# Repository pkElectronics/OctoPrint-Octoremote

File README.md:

# OctoPrint-Octoremote

## Work in Progress! Use with care ##

Octoremote is a system to control serveral functions of your printer with a simple press of a button. Control the axis movement, manual extrusion and homing without the need of navigating through the printer menu or opening the Octopi GUI in your browser. 

OctoRemote consists of two components, the Octoprint plugin and an arduino based hardware controller. The controller and the plugin communicate through a serial connection using a simple byte-based protocol. As OctoRemote is based on Octoprint it is totally printer independent and works easily with any Octorprint compatible printer. At the moment following printer actions are implemented:

* Homing X&Y and Z
* Moving of all axis
* Extrude/Retract material
* Stop Print
* Pause Print
* Start/Resume Print
* Select Extruder
* Select movement distance (4 options)
* User programmable keys Supporting custom GCODE and OctoPrint Scripting

## Setup

Install via the bundled [Plugin Manager](https://github.com/foosel/OctoPrint/wiki/Plugin:-Plugin-Manager)
or manually using this URL:

    https://github.com/pkElectronics/OctoPrint-Octoremote/archive/master.zip

The plugin repository also contains the source code of the Arduino program which is necessary for the hardware controller. Installation if described in detail in the Hardware section.

## Configuration

Use the OctoRemote Plugin page from the Octoprint settings to adjust the parameters to your needs. 

The correct setting for the Comport field is something you have to figure out for yourself, using either for example the Windows device manager or the /dev/tty/\* files under linux. Usually an Arduino UNO will appear as something like /dev/ttyACM0. 

The default settings were developed and tested using an Anet A8 printer.

## Usage

It´s pretty easy, wait for Octoprint to start and start hitting the buttons, movement distance starts at Stage 1 and goes up until Stage 4 with each keypress. From Stage 4 it jumps back to 1. Same holds true for the extruder selection except that it wraps around when the number of configured extruders is reached. Keep in mind that extruding and retracting material only works if the hotend has the right temperature.

## Hardware

There are two possible hardware configurations available, a simple breadboard version using an Arduino UNO, a 4x4 matrix keypad and 8 leds. 

Of course you could build the circuit in a different way, you just have to change the pin assignments in the software.

If you stick to the recommended schematic you will end up with a key assignment like this:

Please Note: User Key 1 is only available when the Tool/Extruder count is 1. Otherwise the key is used to switch between extruders.

In the future there will also be a custom made PCB which includes all necessary parts and uses cherry mx switches for the keys. If you are interested in getting a custom OctoRemote Board
feel free to contact me.
The device is still be compatible with the Arduino IDE for easy upgrading and hacking. Development of the Controller is in pre-production state and will be heading for Kickstarter soon.

Regardless of the type of the used hardware, programming is done using the Arduino IDE and the sourcecodes from the arduino/OctoRemote/ folder.

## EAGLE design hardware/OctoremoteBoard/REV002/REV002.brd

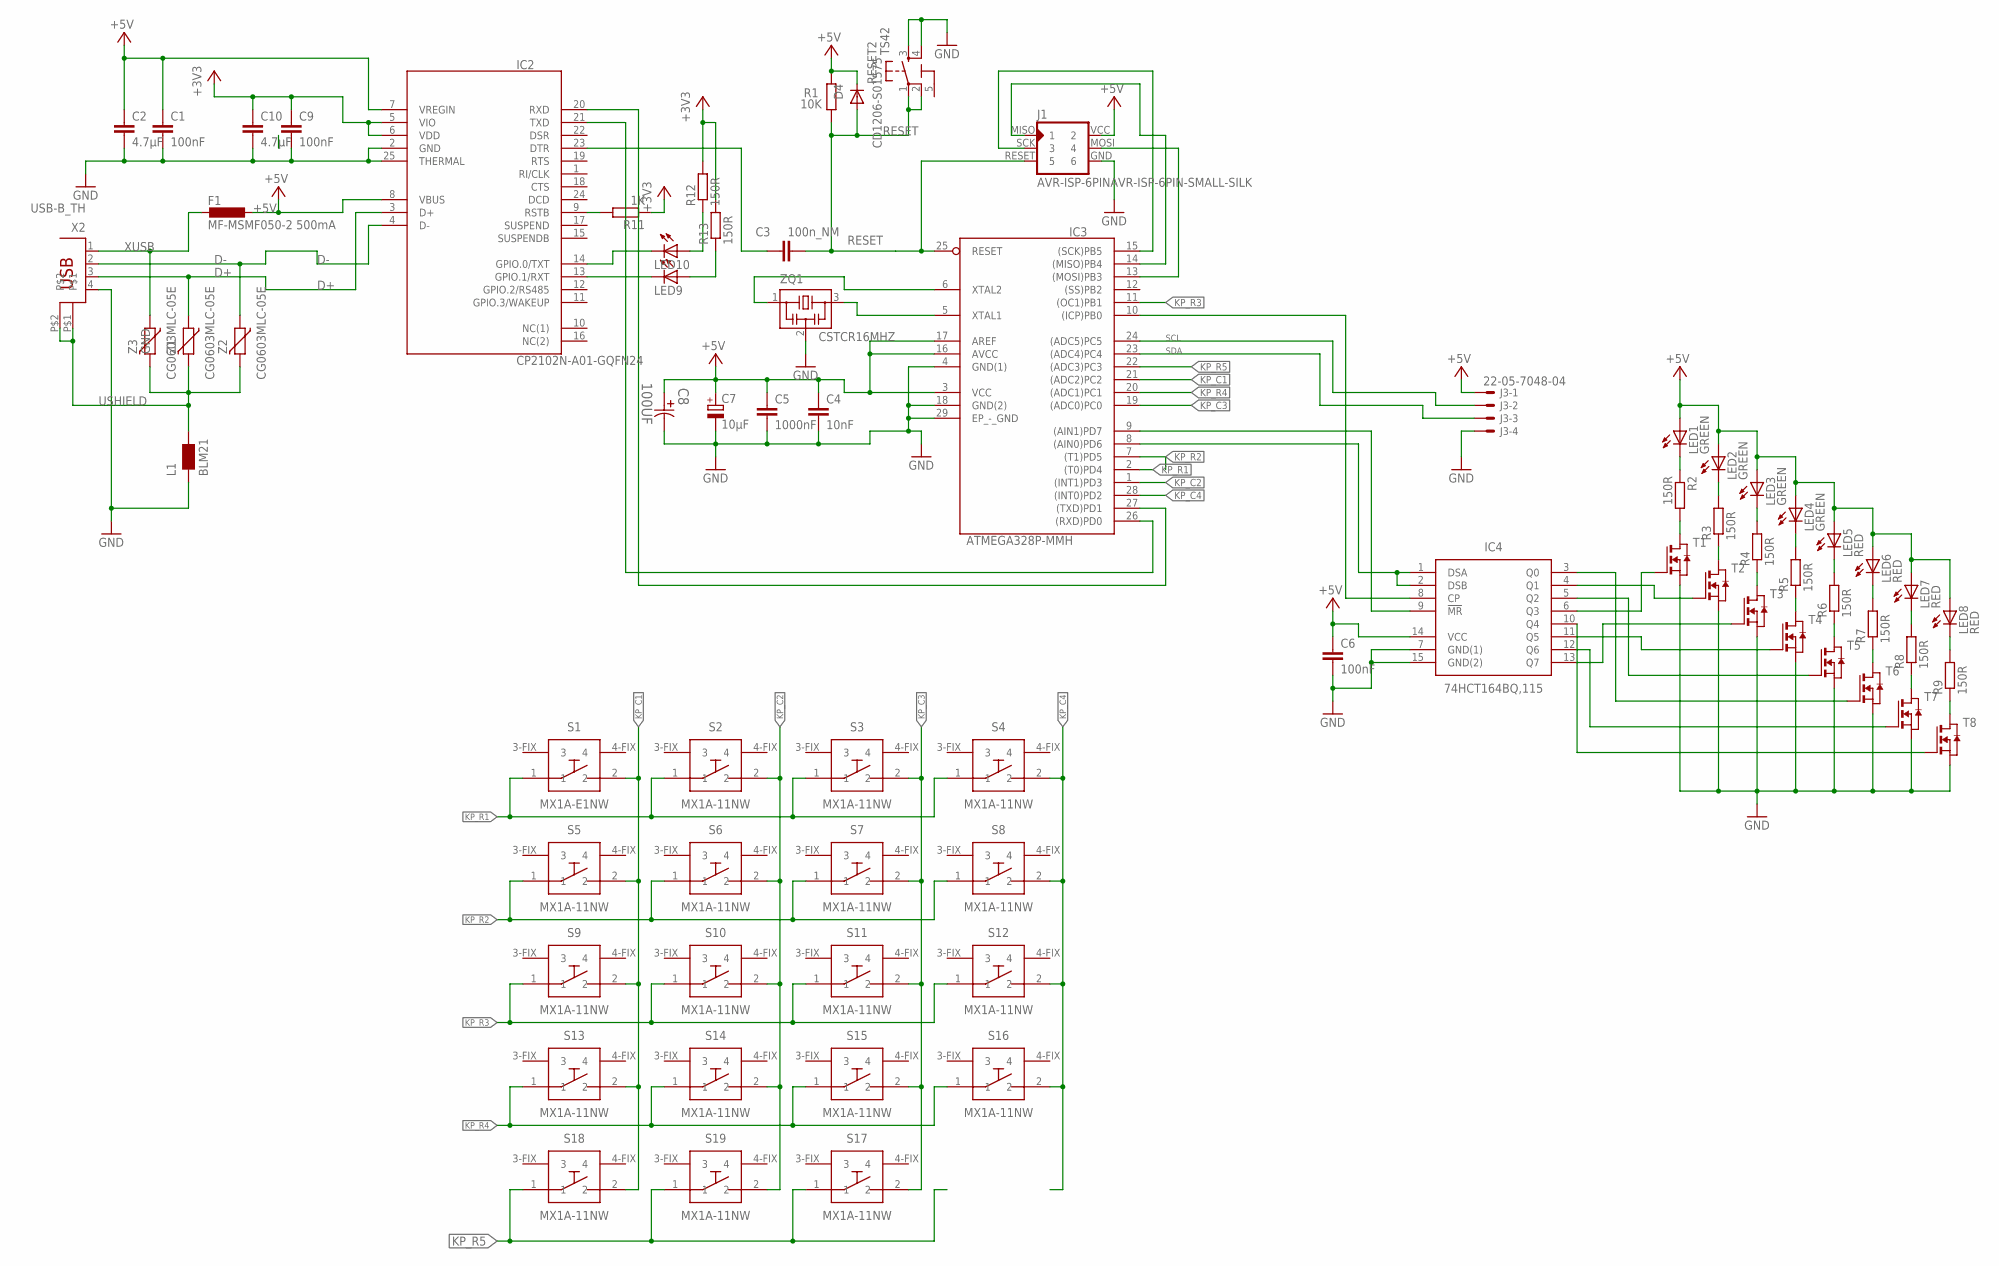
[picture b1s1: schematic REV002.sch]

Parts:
C1, C6, C9: 100nF; C0603K
C2, C10: 4.7µF; C0603K
C3: 100n_NM; C0603K
C4: 10nF; C0603K
C5: 1000nF; C0603K
C7: 10µF; SMC_B
C8: 100UF; CAPAE430X610N
D4: CD1206-S01575; MINIMELF
F1: MF-MSMF050-2 500mA; L1812
IC2: CP2102N-A01-GQFN24; QFN50P400X400X80-25N
IC3: ATMEGA328P-MMH; QFN45P400X400X100-29N
IC4: 74HCT164BQ,115; QFN50P300X250X100-15N
J1: AVR-ISP-6PINAVR-ISP-6PIN-SMALL-SILK; AVR-ISP-6PIN-SMAILL-SILK
J3: 22-05-7048-04; 7395-04
L1: BLM21; 0805
LED1, LED2, LED3, LED4: GREEN; P-LCC-2
LED5, LED6, LED7, LED8: RED; P-LCC-2
LED9, LED10: LEDCHIPLED_0603; CHIPLED_0603
R1: 10K; R0603
R2, R3, R4, R5, R6, R7, R8, R9, R12, R13: 150R; R0603
R11: 1K; R0603
RESET2: TS42
S1: MX1A-E1NW; MX1A-11NW_1
S2, S3, S4, S5, S6, S7, S8, S9, S10, S11, S12, S13, S14, S15, S16, S17, S18, S19: MX1A-11NW; MX1A-11NW_1
T1, T2, T3, T4, T5, T6, T7, T8: NMOSSOT23; SOT-23
X2: USB-B_TH; PN61729
Z1, Z2, Z3: CG0603MLC-05E; CT/CN0603
ZQ1: CSTCR16MHZ; CSTER12M

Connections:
5-GND: RESET2.5 (5-GND)
+3V3: C9.1, C10.1, IC2.5 (VIO), IC2.6 (VDD), R11.1, R12.2, R13.2
+5V: C1.1, C2.1, C4.1, C5.1, C6.1, C7.+, C8.1, D4.C, F1.1, IC2.7 (VREGIN), IC2.8 (VBUS), IC3.3 (VCC), IC3.16 (AVCC), IC3.17 (AREF), IC4.14 (VCC), J1.VCC (2), J3.1, LED1.A, LED2.A, LED3.A, LED4.A, LED5.A, LED6.A, LED7.A, LED8.A, R1.2
D+: IC2.3 (D+), X2.3, Z1.1
D-: IC2.4 (D-), X2.2, Z2.1
GND: C1.2, C2.2, C4.2, C5.2, C6.2, C7.-, C8.2, C9.2, C10.2, IC2.2 (GND), IC2.25 (THERMAL), IC3.4 (GND(1)), IC3.18 (GND(2)), IC3.29 (EP_-_GND), IC4.7 (GND(1)), IC4.15 (GND(2)), J1.GND (6), J3.4, L1.1, RESET2.3, RESET2.4, T1.2 (S), T2.2 (S), T3.2 (S), T4.2 (S), T5.2 (S), T6.2 (S), T7.2 (S), T8.2 (S), X2.4, ZQ1.2
KP_C1: IC3.21 ((ADC2)PC2), S1.2, S5.2, S9.2, S13.2, S18.2
KP_C2: IC3.1 ((INT1)PD3), S2.2, S6.2, S10.2, S14.2, S19.2
KP_C3: IC3.19 ((ADC0)PC0), S3.2, S7.2, S11.2, S15.2, S17.2
KP_C4: IC3.28 ((INT0)PD2), S4.2, S8.2, S12.2, S16.2
KP_R1: IC3.2 ((T0)PD4), S1.1, S2.1, S3.1, S4.1
KP_R2: IC3.7 ((T1)PD5), S5.1, S6.1, S7.1, S8.1
KP_R3: IC3.11 ((OC1)PB1), S9.1, S10.1, S11.1, S12.1
KP_R4: IC3.20 ((ADC1)PC1), S13.1, S14.1, S15.1, S16.1
KP_R5: IC3.22 ((ADC3)PC3), S17.1, S18.1, S19.1
LED1-: LED1.C, R2.1
LED2+: IC3.13 ((MOSI)PB3), J1.MOSI (4)
LED3+: IC3.14 ((MISO)PB4), J1.MISO (1)
LED4+: IC3.15 ((SCK)PB5), J1.SCK (3)
unnamed: IC4.6 (Q3), T1.3 (G)
unnamed: IC2.9 (RSTB), R11.2
unnamed: C3.2, IC2.23 (DTR)
unnamed: IC2.14 (GPIO.0/TXT), LED10.C
unnamed: IC2.13 (GPIO.1/RXT), LED9.C
unnamed: LED10.A, R12.1
unnamed: LED9.A, R13.1
unnamed: IC4.4 (Q1), T2.3 (G)
unnamed: R2.2, T1.1 (D)
unnamed: IC4.13 (Q7), T3.3 (G)
unnamed: IC4.11 (Q5), T4.3 (G)
unnamed: IC4.5 (Q2), T5.3 (G)
unnamed: IC4.3 (Q0), T6.3 (G)
unnamed: IC4.12 (Q6), T7.3 (G)
unnamed: IC4.10 (Q4), T8.3 (G)
unnamed: LED2.C, R3.2
unnamed: R3.1, T2.1 (D)
unnamed: R4.1, T3.1 (D)
unnamed: R5.1, T4.1 (D)
unnamed: R6.1, T5.1 (D)
unnamed: R7.1, T6.1 (D)
unnamed: R8.1, T7.1 (D)
unnamed: R9.1, T8.1 (D)
unnamed: LED8.C, R9.2
unnamed: LED7.C, R8.2
unnamed: LED6.C, R7.2
unnamed: LED5.C, R6.2
unnamed: LED4.C, R5.2
unnamed: LED3.C, R4.2
unnamed: IC3.10 ((ICP)PB0), IC4.8 (CP)
unnamed: IC3.8 ((AIN0)PD6), IC4.1 (DSA), IC4.2 (DSB)
unnamed: IC3.9 ((AIN1)PD7), IC4.9 (!MR)
RESET: C3.1, D4.A, IC3.25 (RESET), J1.RESET (5), R1.1, RESET2.1, RESET2.2
RX: IC2.20 (RXD), IC3.27 ((TXD)PD1)
SCL: IC3.24 ((ADC5)PC5), J3.2
SDA: IC3.23 ((ADC4)PC4), J3.3
TX: IC2.21 (TXD), IC3.26 ((RXD)PD0)
USHIELD: L1.2, X2.P$1, X2.P$2, Z1.2, Z2.2, Z3.2
XTAL1: IC3.5 (XTAL1), ZQ1.3
XTAL2: IC3.6 (XTAL2), ZQ1.1
XUSB: F1.2, X2.1, Z3.1

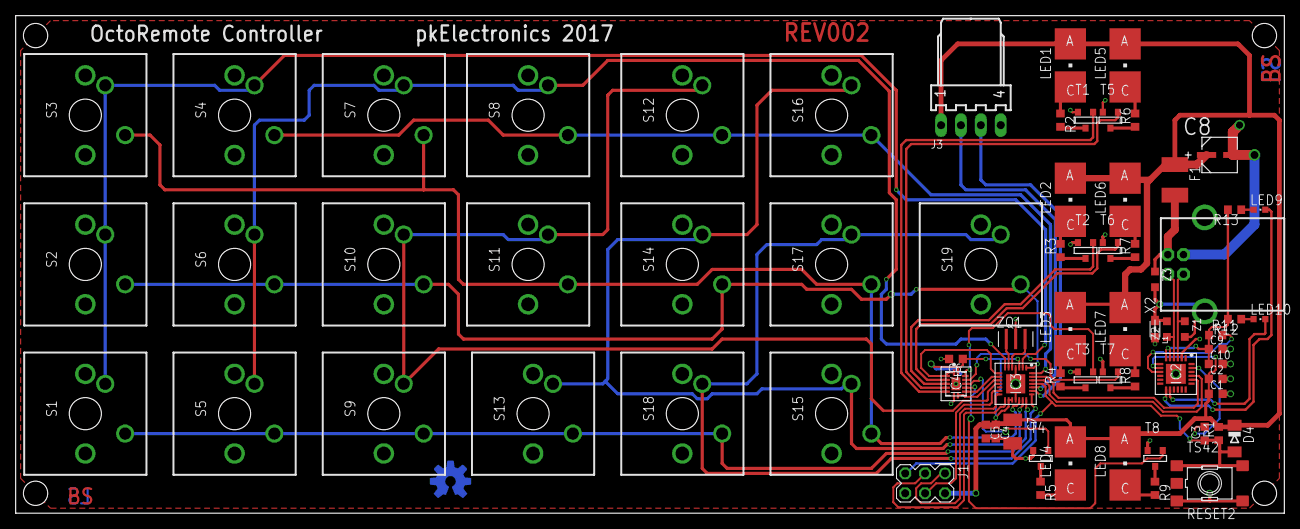
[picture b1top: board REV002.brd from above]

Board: 2 copper layers, 161.9 x 63.5 mm, 74 parts (1 on the bottom side), 59 nets.

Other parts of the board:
U$1: OSHWLOGO_TOP_0.2

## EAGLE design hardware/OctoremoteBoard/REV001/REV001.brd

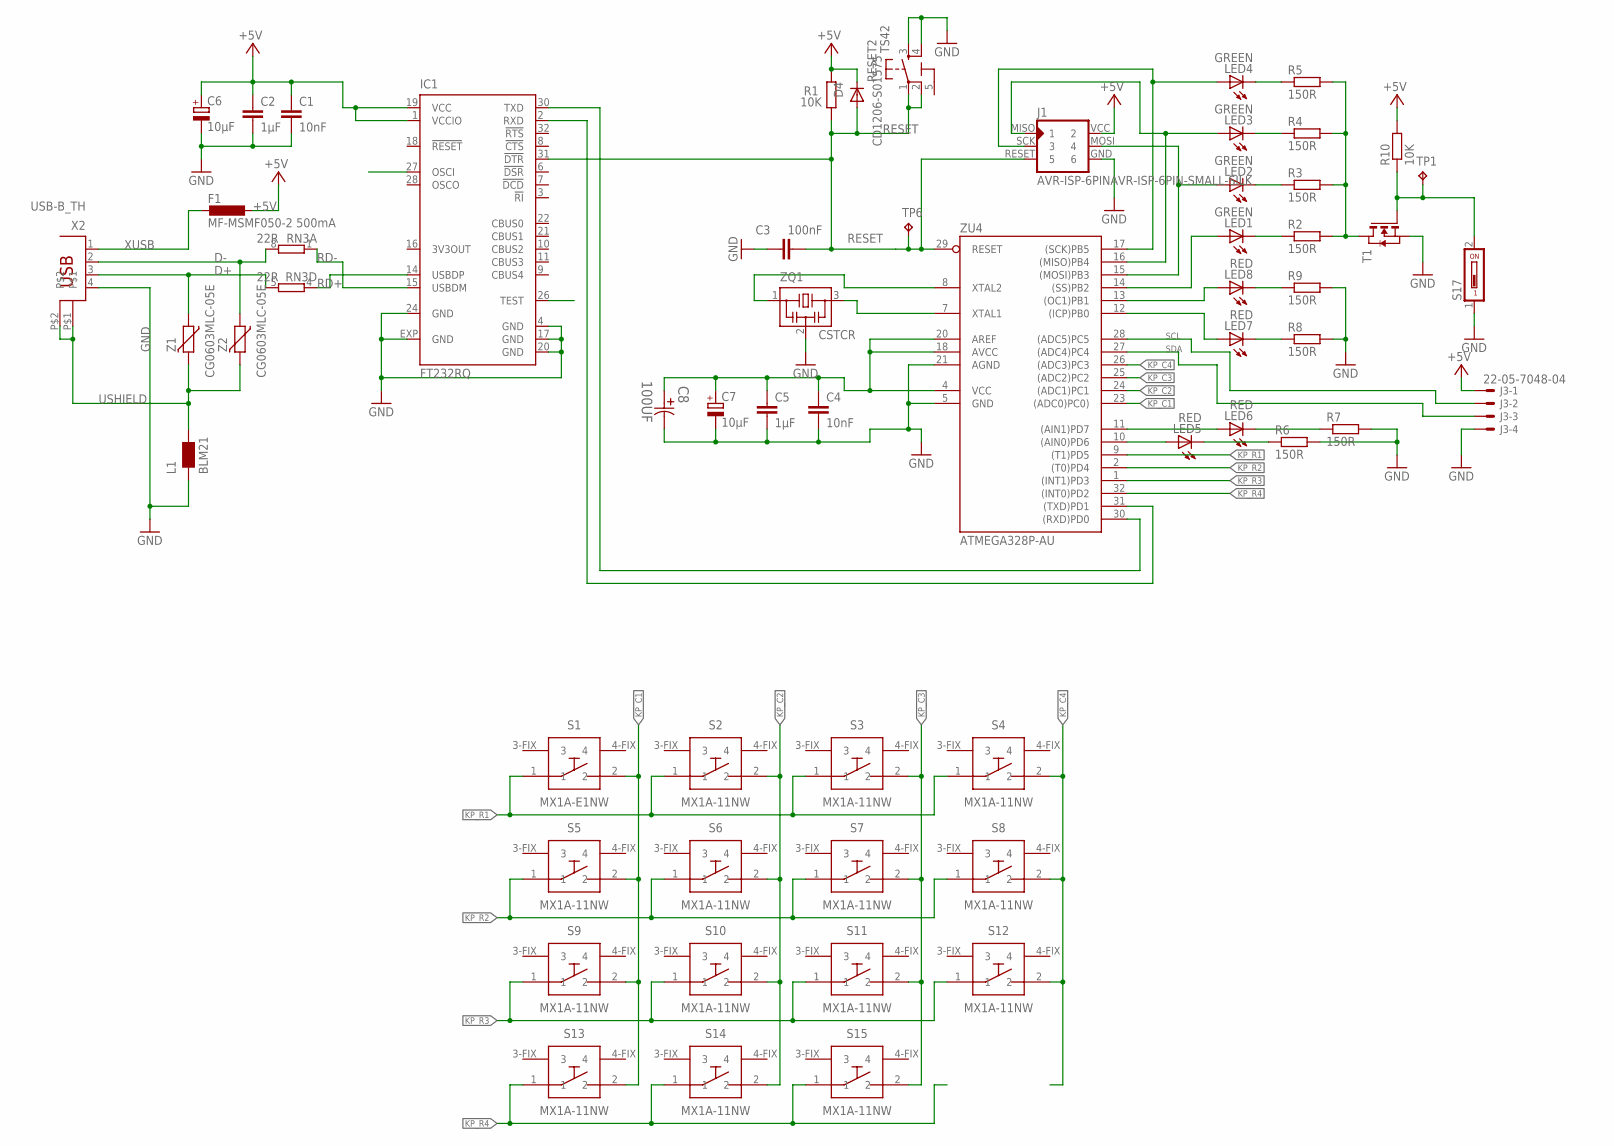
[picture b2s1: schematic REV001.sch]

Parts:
C1, C4: 10nF; C0603K
C2, C5: 1µF; C0603K
C3: 100nF; C0603-ROUND
C6, C7: 10µF; SMC_B
C8: 100UF; CAPAE430X610N
D4: CD1206-S01575; MINIMELF
F1: MF-MSMF050-2 500mA; L1812
IC1: FT232RQ; QFN32
J1: AVR-ISP-6PINAVR-ISP-6PIN-SMALL-SILK; AVR-ISP-6PIN-SMAILL-SILK
J3: 22-05-7048-04; 7395-04
L1: BLM21; 0805
LED1, LED2, LED3, LED4: GREEN; P-LCC-2
LED5, LED6, LED7, LED8: RED; P-LCC-2
R1, R10: 10K; R0805
R2, R3, R4, R5, R6, R7, R8, R9: 150R; R0805
RESET2: TS42
RN3: 22R; CAY16
S1: MX1A-E1NW; MX1A-11NW_1
S2, S3, S4, S5, S6, S7, S8, S9, S10, S11, S12, S13, S14, S15: MX1A-11NW; MX1A-11NW_1
S17: DS01; DS-01
T1: NMOSSOT23; SOT-23
TP1, TP6: TPB1,27; B1,27
X2: USB-B_TH; PN61729
Z1, Z2: CG0603MLC-05E; CT/CN0603
ZQ1: CSTCR; CSTER12M
ZU4: ATMEGA328P-AU; TQFP32-08

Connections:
5-GND: RESET2.5 (5-GND)
+5V: C1.1, C2.1, C4.1, C5.1, C6.+, C7.+, C8.1, D4.C, F1.1, IC1.1 (VCCIO), IC1.19 (VCC), J1.VCC (2), J3.1, R1.2, R10.2, ZU4.4 (VCC), ZU4.18 (AVCC), ZU4.20 (AREF)
D+: RN3.5 (2), X2.3, Z1.1
D-: RN3.8 (2), X2.2, Z2.1
GND: C1.2, C2.2, C3.2, C4.2, C5.2, C6.-, C7.-, C8.2, IC1.4 (GND), IC1.17 (GND), IC1.20 (GND), IC1.24 (GND), IC1.EXP (GND), J1.GND (6), J3.4, L1.1, R6.2, R7.2, R8.2, R9.2, RESET2.3, RESET2.4, S17.1, T1.2 (S), X2.4, ZQ1.2, ZU4.5 (GND), ZU4.21 (AGND)
ISP_ENABLE: R10.1, S17.2, T1.3 (G), TP1.TP
KP_C1: S1.2, S5.2, S9.2, S13.2, ZU4.23 ((ADC0)PC0))
KP_C2: S2.2, S6.2, S10.2, S14.2, ZU4.24 ((ADC1)PC1)
KP_C3: S3.2, S7.2, S11.2, S15.2, ZU4.25 ((ADC2)PC2)
KP_C4: S4.2, S8.2, S12.2, ZU4.26 ((ADC3)PC3)
KP_R1: S1.1, S2.1, S3.1, S4.1, ZU4.9 ((T1)PD5)
KP_R2: S5.1, S6.1, S7.1, S8.1, ZU4.2 ((T0)PD4)
KP_R3: S9.1, S10.1, S11.1, S12.1, ZU4.1 ((INT1)PD3)
KP_R4: S13.1, S14.1, S15.1, ZU4.32 ((INT0)PD2)
LED1+: LED1.A, ZU4.14 ((SS)PB2)
LED1-: LED1.C, R2.1
LED2+: J1.MOSI (4), LED2.A, ZU4.15 ((MOSI)PB3)
LED2-: LED2.C, R3.1
LED3+: J1.MISO (1), LED3.A, ZU4.16 ((MISO)PB4)
LED3-: LED3.C, R4.1
LED4+: J1.SCK (3), LED4.A, ZU4.17 ((SCK)PB5)
LED4-: LED4.C, R5.1
LED5+: LED5.A, ZU4.10 ((AIN0)PD6)
LED5-: LED5.C, R6.1
LED6+: LED6.A, ZU4.11 ((AIN1)PD7)
LED6-: LED6.C, R7.1
LED7+: LED7.A, ZU4.12 ((ICP)PB0)
LED7-: LED7.C, R8.1
LED8+: LED8.A, ZU4.13 ((OC1)PB1)
LED8-: LED8.C, R9.1
unnamed: R2.2, R3.2, R4.2, R5.2, T1.1 (D)
RD+: IC1.14 (USBDP), RN3.4 (1)
RD-: IC1.15 (USBDM), RN3.1
RESET: C3.1, D4.A, IC1.31 (!DTR), J1.RESET (5), R1.1, RESET2.1, RESET2.2, TP6.TP, ZU4.29 (RESET)
RX: IC1.2 (RXD), ZU4.31 ((TXD)PD1)
SCL: J3.2, ZU4.28 ((ADC5)PC5)
SDA: J3.3, ZU4.27 ((ADC4)PC4)
TX: IC1.30 (TXD), ZU4.30 ((RXD)PD0)
USHIELD: L1.2, X2.P$1, X2.P$2, Z1.2, Z2.2
XTAL1: ZQ1.3, ZU4.7 (XTAL1)
XTAL2: ZQ1.1, ZU4.8 (XTAL2)
XUSB: F1.2, X2.1

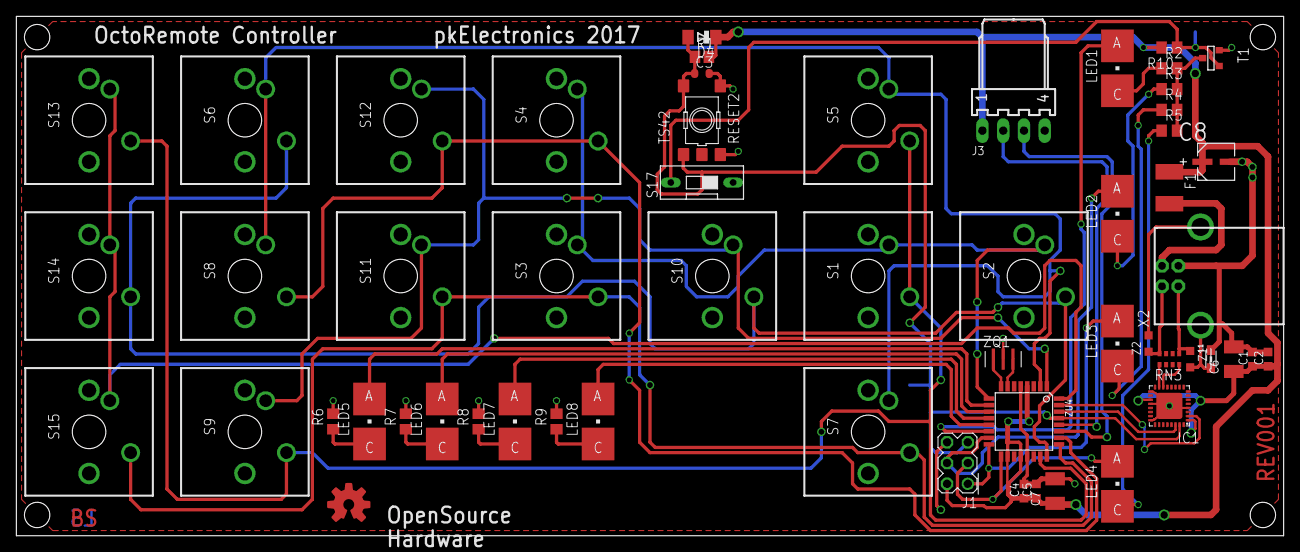
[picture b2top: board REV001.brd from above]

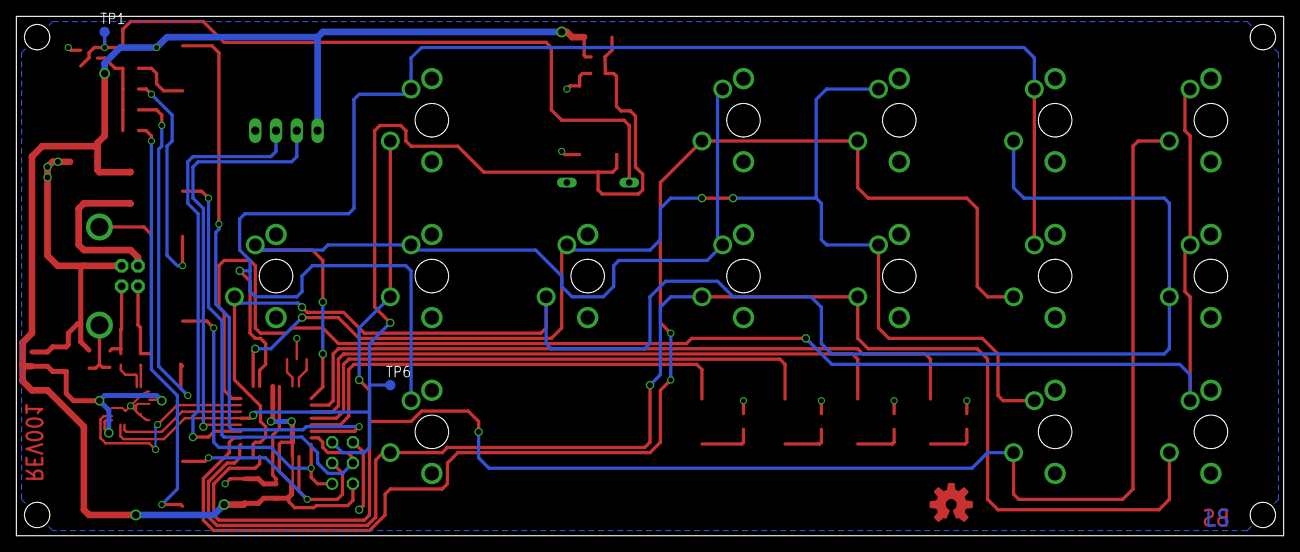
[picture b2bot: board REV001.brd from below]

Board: 2 copper layers, 154.9 x 63.5 mm, 59 parts (2 on the bottom side), 41 nets.

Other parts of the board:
U$1: OSHWLOGO_TOP_0.2

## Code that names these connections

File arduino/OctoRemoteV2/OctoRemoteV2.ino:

// =============================================================================
//
// Copyright (c) 2017 Pascal Krumme
//
// Permission is hereby granted, free of charge, to any person obtaining a copy
// of this software and associated documentation files (the "Software"), to deal
// in the Software without restriction, including without limitation the rights
// to use, copy, modify, merge, publish, distribute, sublicense, and/or sell
// copies of the Software, and to permit persons to whom the Software is
// furnished to do so, subject to the following conditions:
//
// The above copyright notice and this permission notice shall be included in
// all copies or substantial portions of the Software.
//
// THE SOFTWARE IS PROVIDED "AS IS", WITHOUT WARRANTY OF ANY KIND, EXPRESS OR
// IMPLIED, INCLUDING BUT NOT LIMITED TO THE WARRANTIES OF MERCHANTABILITY,
// FITNESS FOR A PARTICULAR PURPOSE AND NONINFRINGEMENT. IN NO EVENT SHALL THE
// AUTHORS OR COPYRIGHT HOLDERS BE LIABLE FOR ANY CLAIM, DAMAGES OR OTHER
// LIABILITY, WHETHER IN AN ACTION OF CONTRACT, TORT OR OTHERWISE, ARISING FROM,
// OUT OF OR IN CONNECTION WITH THE SOFTWARE OR THE USE OR OTHER DEALINGS IN
// THE SOFTWARE.
//
// =============================================================================
// Requires CRC32 Library by Christopher Baker 
// Requires Keypad Library by Mark Stanley and Alexander Brevig
// Available through the Arduino Library Manager

#include <CRC32.h>
#include <Keypad.h>

//DATA PD6 -> D6
//CLOCK PB0 -> D8
//RESET PD7 -> D7

#define SR_RESET 7
#define SR_DATA 6
#define SR_CLOCK 8

const byte ROWS = 5; //five rows
const byte COLS = 4; //four columns
//define the cymbols on the buttons of the keypads
char hexaKeys[ROWS][COLS] = {
  {0x43,0x42,0x41,0x22},
  {0x24,0x51,0x34,0x14},
  {0x31,0x33,0x13,0x52},
  {0x41,0x32,0x23,0x21},
  {0x53,0x12,0x11,0x54}
};
byte rowPins[ROWS] = {4, 5, 9, A1 , A3}; //connect to the row pinouts of the keypad PD4 , PD5, PB1, PC1, PC3
byte colPins[COLS] = {A2, 3 , A0, 2}; //connect to the column pinouts of the keypad PC2 , PD3, PC0, PD2

#define TRANSMISSION_HEADER 0x80
#define COMMAND_KEYPRESSED 0x10
#define COMMAND_KEYRELEASED 0x11
#define COMMAND_KEYHOLD 0x12
#define COMMAND_SETLED 0x20

#define COMMAND_ACK 0x01
#define COMMAND_NACK 0x02

//initialize an instance of class NewKeypad
Keypad customKeypad = Keypad( makeKeymap(hexaKeys), rowPins, colPins, ROWS, COLS); 
CRC32 crc;

char ackPending = false;
long lastSendTime = 0;
char lastSendKey = 0;
char lastSendCMD = 0;
uint8_t retryCounter = 0;


void writeByteToSR(byte data){
  for(int i = 0 ; i < 8 ; i++){
    PORTB &= ~(1<<PB0);
    if( (data >> i ) & 1 == 1){
      PORTD |= 1 << PD6;
    }else{
      PORTD &= ~(1<<PD6);
    }
    PORTB |= (1<<PB0);
   }
}


void setup(){
  Serial.begin(115200);
  customKeypad.addEventListener(keypadEvent);

  pinMode(SR_RESET,OUTPUT);
  pinMode(SR_DATA,OUTPUT);
  pinMode(SR_CLOCK,OUTPUT);

  digitalWrite(SR_RESET,HIGH);

   pinMode(SR_RESET,OUTPUT);
  pinMode(SR_DATA,OUTPUT);
  pinMode(SR_CLOCK,OUTPUT);

  digitalWrite(SR_RESET,HIGH);
  for(int i = 0 ; i < 8 ; i++){
    setLeds(1<<i);
    delay(300);
  }
  setLeds(0);
}



void keypadEvent(KeypadEvent key){
    switch (customKeypad.getState()){
    case PRESSED:
        sendKeyToHost(key,COMMAND_KEYPRESSED);
        break;

    case RELEASED:
        sendKeyToHost(key,COMMAND_KEYRELEASED);
        break;

    case HOLD:
        sendKeyToHost(key,COMMAND_KEYHOLD);
        break;
    }
}

long lastcall = 0L;
unsigned char ledIndex = 0;

unsigned char telegramLength = 0;
unsigned char telegramCommand = 0;
unsigned char payload[256];
unsigned char payloadIndex = 0;
unsigned char parsingState = 0;
uint32_t telegramCRC = 0;

  
void loop(){
  char key = customKeypad.getKey();
  if(ackPending && (millis()- lastSendTime > 2000) && retryCounter < 3){
    resendLastCommand();
    retryCounter++;
  }
  handleSerial();
}

int row1 = 0;
int row2 = 0;

void setLeds(byte b){
  byte ledOut = 0;

  switch(b){
    case 0:
      row1 = 1<<4;
      break;
    case 1:
      row1 = 1<<6;
      break;
    case 2:
      row1 = 1<<0;
      break;
    case 3:
      row1 = 1<<2;
      break;
    case 4:
    row2 = 1<<5;
    break;
    case 5:
    row2 = 1<<7;
    break;
    case 6:
    row2 = 1<<1;
    break;
    case 7:
    row2 = 1<<3;
    break;
    default:
    break;
  }
  writeByteToSR(row1|row2);
  
}

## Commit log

2017-03-23 :boom::camel: Added .gitattributes & .gitignore files
2017-03-23 Revert ":boom::camel: Added .gitattributes & .gitignore files"
    This reverts commit a8a949d086af2c4f846fe9bd64f058f7eef00ca1.
2017-03-23 Revert "Revert ":boom::camel: Added .gitattributes & .gitignore files""
    This reverts commit 4ed2bfe0b78432cde22c74f73e441e2c8bd922de.
2017-03-23 Kekse
2017-03-23 Doing stuff
2017-03-24 Updated Readme
    Dokumentation added
2017-03-26 First "working" commit
2017-03-29 Development Commit
2017-03-29 cleanup
2017-03-29 Kleinkram
2017-03-29 Added License Info
2017-04-01 Bugfix
    (Hopefully) fixed bug that prevented settings from being saved
2017-04-01 Fixed settings problems
2017-04-01 Fixed stuff
2017-04-04 Fixed Settings Issue
2018-02-03 Update for Hardware Revision 3
    Added Support for User Programmable Keys
    Added Arduino Code for HW Revision 3
2018-02-03 Updated Setup.py for Pluginmanager
    Changed Version to 0.2
2018-02-03 Updated Documentation
